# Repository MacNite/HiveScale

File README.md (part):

# HiveHub

> **Project renamed: HiveScale → HiveHub.** The project outgrew its original
> "dual scale" scope and now acts as a **data collector / hub for many different
> types of beehive sensors and scales** (up to 16 hives per ESP32), so the name
> was changed to match. A few internal identifiers — the database measurement
> columns, the OTA `target` value, the Docker image name (`…/hivescale-api`), the
> device's stored-config (NVS) namespace and MQTT topics — still use the old
> `hivescale` name on purpose: changing them would need data/firmware migrations
> and could strand existing measurements or deployed-device config. The
> third-party **beehivemonitoring.com "HiveScale"** wireless weight scale is an
> unrelated product and keeps its own name.

**Hardware status: all published PCBs are tested and working.** The recommended build is the **XIAO ESP32-C6 on the Scale Module V0.4** with **NAU7802**, **MAX17048**, **TPS63020**, **TP4056**, RTC, SD card and SHT40 — optionally expanded to **16 scales** with the NAU7802 breakout PCB (TCA9548A mux + up to 8× NAU7802). See [pcb-design/README.md](pcb-design/README.md). The old ESP32 30-pin board is obsolete and no longer recommended.

**HiveHub is an ESP32-based data collector for beehive sensors and scales.** It
gathers weight, temperature, humidity, sound, vibration, power state, and network
state from one or more hives (up to 16 per ESP32) and sends the readings to a
self-hosted FastAPI backend backed by PostgreSQL, where they can be displayed in
[HivePal](https://github.com/martinhrvn/hive-pal).

### Natively supported sensors

Every sensor is optional and compiled in per device — HiveHub reads the
following directly on the ESP32:

- **Ambient sensor (SHT4x / SHT3x / BME280)** — one device-level outside-hive
  sensor on the shared I2C bus, selectable at build time: SHT4x/SHT40 (default)
  or SHT3x for temperature + humidity, or a BME280 which additionally reports
  barometric pressure (`ambient_pressure_hpa`).
- **DS18B20** — per-hive in-hive temperature probes (1-Wire).
- **INMP441** — in-hive sound via I2S MEMS microphones with per-band FFT.
- **MAX17048** — LiPo battery voltage, state-of-charge, and low-battery alerts (I2C).
- **Wired load cells via HX711 or NAU7802** — the hive scales themselves; NAU7802
  over I2C (optionally behind a TCA9548A mux) scales to many channels for
  multi-hive setups.

On top of these wired sensors, HiveHub also bridges a range of wireless BLE/GATT
sensors and scales (HolyIot, RuuviTag, HiveInside, and beehivemonitoring.com
HiveHeart / HiveScale devices) — see [Features](#features) below.

> 🌐 **Website & setup guide:** a small static site lives in [`website/`](website/) — a
> feature overview, a step-by-step setup guide, a complete
> ["Build your own" guide](website/build.html) (BOM with price estimates, wiring,
> firmware, backend — downloadable as PDF), and an in-browser
> [`secrets.h` configurator](website/configurator.html) that builds your firmware
> config (sensors, BLE/GATT options, power modules) without hand-editing macros.
> It deploys to GitHub Pages via `.github/workflows/pages.yml`
> (enable **Settings → Pages → Source: GitHub Actions**), e.g.
> `https://macnite.github.io/HiveHub/`.

---

## Features

Every sensor is optional and compiled in per device — start with weight and add the rest.

- **Dual load cells** — two HX711 amplifiers drive two independent hive scales (the one always-on measurement).
- **Backend load-cell temperature compensation** — corrects HX711 thermal drift on read from the stored raw values; see [docs/temperature-compensation.md](docs/temperature-compensation.md).
- **Per-hive temperature** — optional DS18B20 probes on a shared 1-Wire bus (off by default), or an in-hive BLE sensor as the source.
- **Per-hive in-hive sound** — optional INMP441 stereo I2S microphones with per-band FFT (off by default).
- **Per-hive vibration** — from a paired in-hive BLE sensor (a HiveInside nRF54LM20A gives full FFT bands; a HolyIot/RuuviTag beacon gives a low-rate magnitude), capturing the ~20 Hz pre-swarm signal microphones miss. (The old wired LIS3DH/LIS2DH12 driver has been removed — in-hive vibration is BLE-only.)
- **In-hive BLE sensors** — pair up to two battery beacons (HolyIot 25015, RuuviTag, HiveInside nRF54LM20A, or beehivemonitoring.com HiveHeart) for temperature/humidity/pressure/vibration with no wiring. Note that a HiveHeart is read over GATT and accepts only **one** connection at a time, so HiveHub, the beehivemonitoring Hub and the beehivemonitoring app cannot share one — see [beehivemonitoring-gatt.md](docs/beehivemonitoring-gatt.md#one-reader-at-a-time).
- **Ambient temperature & humidity** — one selectable device-level I2C sensor: SHT4x/SHT40 (default), SHT3x, or a BME280 that also reports barometric pressure (`ambient_pressure_hpa`). Picked at build time (`ENABLE_SHT4X_AMBIENT` / `ENABLE_SHT3X_AMBIENT` / `ENABLE_BME280_AMBIENT`).
- **RTC timekeeping** — a DS3231 timestamps measurements without depending on NTP.
- **SD card cache & backup** — local buffering when uploads fail, plus an append-only persistent backup that can be downloaded in AP mode and re-imported via HivePal.
- **Claim-code pairing** — claim devices from HivePal without manual database setup.
- **Remote configuration & commands** — sampling interval, scale offsets/factors, calibration, OTA checks, provisioning, reboot, Wi-Fi reset, and factory reset.
- **OTA firmware updates** — owner-scoped releases with an accept-to-apply gate; the device also relays firmware over BLE GATT to a HiveInside sensor or a HiveTraffic counter. Both relays are version-gated and explicit: publishing a release never pushes it to a sub-device on its own.
- **Wi-Fi provisioning portal** — opened by the setup button (or remotely with a `start_provisioning` command) for field configuration, including pairing wireless sensors.
- **[Inspection mode](docs/inspection-mode.md)** — one press of the external button, a dashboard switch or a HivePal API call marks the window while a hive is open, so the 40 kg step from lifting two supers stays out of the charts, insights and alert rules. Nothing is deleted: the readings remain in the database and in every export.
- **Multi-network Wi-Fi** — up to three saved networks.
- **Hive audio (optional)** — ask a paired HiveInside node (firmware 0.6.2+) to record 10–60 seconds from inside the hive, then play it back in the dashboard. The hub collects the request on its next wake, so a recording arrives within one reporting interval rather than instantly. Authenticated with a shared key and stored as WAV on your own server. Useful for checking what an insight flagged — or just for listening to the bees. See [Listening to a hive](docs/audio-recording.md).
- **Insights** — backend auto-evaluation of weight, temperature, sound, vibration, and entrance traffic per hive, based on [these publications](docs/insights-sources-tldr.md).
- **Insight alert notifications (optional)** — get swarm / robbing / winter-risk alerts by **e-mail (SMTP)** and/or **Web Push** to your phone or an installable dashboard PWA (Android, iOS 16.4+, desktop) when an insight first fires or escalates. Off by default; see [Insight alert notifications](docs/notifications.md).
- **Optional off-grid mode** — solar/LiPo charging (CN3791 MPPT + TPS63020) with MAX17048 LiPo telemetry.
- **Optional entrance bee counters** — wireless [HiveTraffic](docs/hivetraffic-bee-counter.md) counters over **BLE/GATT only** (wired I2C BeeCounters are no longer supported).
- **Built-in web dashboard (optional)** — a dependency-free dashboard served from the backend at `/dashboard` for single-owner self-hosts, protected by **username + password login** (first visit runs a setup wizard; admin/viewer roles): cross-device hive comparison, charts for every data group, plus device-config editing, hive renaming, firmware/OTA and calibration controls, SD-backup import, and user management. Off by default (`ENABLE_LOCAL_DASHBOARD`); see [server/dashboard/README.md](server/dashboard/README.md) and the [live demo](https://macnite.github.io/HiveHub/dashboard-demo/).
- **Publish data for your website** — from **Device & admin → Publish data**, publish one chart (a metric, the hives you pick, a rolling period) and embed it in a club page, blog or shop with a one-line `<iframe>` — or fetch the same slice as JSON/CSV and draw it yourself. Everything else stays behind the login: a published link exposes only the labels you typed, no device IDs or other readings, and can be revoked at any time. See [Publish data](docs/publish-embed.md).
- **[HivePal](https://github.com/martinhrvn/hive-pal) integration** — dedicated `/api/v1/app/...` endpoints using a HivePal service key, per-user JWTs, and per-user access roles.
- **Optional MQTT bridge** — mirror every reading to an MQTT broker (Home Assistant, Node-RED, openHAB…) with Home Assistant auto-discovery, alongside the built-in PostgreSQL store. Off by default; see [MQTT / Home Assistant integration](#mqtt--home-assistant-integration).
- **PCB designs (tested and working)** — KiCad ESP32-C6 Scale Module (recommended) and NAU7802 breakout board with fabrication outputs, plus the Power Module and legacy 30-pin Scale Module.
- **Docker Compose deployment** — the API and PostgreSQL database.

---

## Repository structure

```text
HiveHub/
├── firmware/                   # ESP32 PlatformIO project (src/, include/)
├── server/                     # Python FastAPI backend, insights, migrations
│   ├── dashboard/              # Built-in login-protected web dashboard (served at /dashboard)
│   └── embed/                  # Public "Publish data" chart pages (served at /embed/chart/<token>)
├── docker/                     # Docker Compose deployment
├── website/                    # Static site + secrets.h configurator (GitHub Pages)
│   └── dashboard-demo/         # Backend-free dashboard demo (sample data)
├── docs/                       # Hardware, API, deployment, and feature docs
├── pcb-design/                 # KiCad breakout PCB design and fabrication files
├── test-data/                  # Mock server and decoder/insight unit tests
└── .github/workflows/          # CI: backend image build + website Pages deploy
```

---

## Hardware

### Core components

All links are affiliate links and support this project directly.

The recommended build is the **XIAO ESP32-C6 on the Scale Module V0.4** — the complete
bill of materials with price estimates and shop links lives on the
[**Build your own** page](website/build.html) (also downloadable as
[CSV](website/assets/hivehub-bom.csv)).

| Component | Role |
|---|---|
| Seeed Studio XIAO ESP32-C6 | Main controller (**recommended** — plugs into the Scale Module V0.4 PCB) |
| NAU7802 (I2C, on the Scale Module / breakout PCB) + [load cells](https://s.click.aliexpress.com/e/_c33VsCl7) | Weight measurement (**recommended** — 2 scales on the Scale Module, up to 16 via the NAU7802 breakout PCB with its TCA9548A mux + up to 8× NAU7802) |
| [SHT4x / SHT40](https://s.click.aliexpress.com/e/_c3CvaIKz) (or SHT3x / BME280) | Ambient temperature and humidity (BME280 also adds barometric pressure) |
| [DS3231 RTC](https://s.click.aliexpress.com/e/_c4mfPBtR) | Offline timekeeping (remove its 4.7 kΩ I2C pull-ups — see the I2C pull-up note in [docs/wiring.md](docs/wiring.md)) |
| [MicroSD card module](https://s.click.aliexpress.com/e/_c3oDcFM9) + card | Local cache and backup storage |
| [MAX17048](https://s.click.aliexpress.com/e/_c3JKEzrL) | LiPo battery gauge (on the Scale Module) |
| [TPS63020 buck-boost](https://s.click.aliexpress.com/e/_c2uscIy1) | Battery/5 V input to the regulated 3.3 V rail |
| [TP4056 USB-C charger](https://s.click.aliexpress.com/e/_c4beU1nL) | LiPo charging |
| [Momentary pushbutton](https://s.click.aliexpress.com/e/_c4sqg7Lx) | Provisioning and factory reset |
| [IP-rated enclosure](https://s.click.aliexpress.com/e/_c30msn9R), [glands](https://de.aliexpress.com/item/1005007921366362.html), frame hardware | Outdoor installation |
| [ESP32 Dev Board](https://s.click.aliexpress.com/e/_c3LV3nfF) + 2x [HX711](https://s.click.aliexpress.com/e/_c3DkGsAN) | Legacy 30-pin build (obsolete — no longer recommended) |

### Optional sensors (enable per device in `secrets.h`)

| Component | Firmware flag | Role |
|---|---|---|
| 2x [DS18B20 waterproof probes](https://s.click.aliexpress.com/e/_c4X4ktmv) | `ENABLE_DS18B20_HIVE_TEMP` | Internal hive temperature (or use an in-hive BLE sensor) |
| 2x [INMP441 sound sensors](https://s.click.aliexpress.com/e/_c313NoAd) | `ENABLE_INMP441_MICS` | Internal hive sound with per-band FFT |
| [MAX17048](https://s.click.aliexpress.com/e/_c3JKEzrL) | `ENABLE_MAX17048_BATTERY` | LiPo voltage, state-of-charge, and low-battery alert |
| In-hive BLE sensor (HolyIot 25015 / RuuviTag / HiveInside / HiveHeart) | `ENABLE_BLE_SCAN`, `ENABLE_BEEHIVE_GATT` | Temp / humidity / pressure / vibration, no wiring — paired by MAC |
| [CN3791 solar charger](https://s.click.aliexpress.com/e/_c4T7Ve5x) · [10 Ah LiPo](https://s.click.aliexpress.com/e/_c45jfAGv) · [6 V 4.5 W solar panel](https://s.click.aliexpress.com/e/_c3njKuVF) | Hardware only | Off-grid charging path feeding the Scale Module's TPS63020 |

### Optional bee counters

Entrance traffic counting (in/out bees) is **BLE/GATT-only**:

- **HiveTraffic** — the wireless [2026-easy-bee-counter](https://github.com/MacNite/2026-easy-bee-counter) board; see [docs/hivetraffic-bee-counter.md](docs/hivetraffic-bee-counter.md). Pairable to any hive.
- Wired I2C BeeCounters (the old `0x30`/`0x31` slave path, including firmware updates over I2C) are **no longer supported**. BeeCounter firmware is updated over BLE GATT instead — see [hivetraffic-bee-counter.md](docs/hivetraffic-bee-counter.md).

### Firmware pin mapping

Pins are defined in `firmware/include/config.h` (with optional per-device overrides in `secrets.h`). The firmware source is split into focused units under `firmware/src/` (`main.cpp`, `hivehub_network.cpp`, `portal.cpp`, `sensors.cpp`, `scale_bus.cpp`, `i2c_bus.cpp`, `hive_config.cpp`, `mics.cpp`, `ble_sensor.cpp`, `beehive_gatt.cpp`, `bee_counter_client.cpp`, `storage_power.cpp`, `device_prefs.cpp`, `status_led.cpp`, `globals.cpp`).

The table below is the **legacy 30-pin ESP32** map. The recommended **XIAO ESP32-C6** build (`pio run -e xiao_esp32c6`) has its own pin map — NAU7802 scales over I2C on D4/D5, DS18B20 on D1, SD on D3/D8–D10, button on D2, no HX711/INMP441 — see [docs/wiring.md](docs/wiring.md) and [pcb-design/README.md](pcb-design/README.md).

| Signal | GPIO | Notes |
|---|---:|---|
| HX711 #1 DOUT / SCK | 16 / 17 | Scale 1; SCK held high during deep sleep to power down the HX711 |
| HX711 #2 DOUT / SCK | 32 / 33 | Scale 2; SCK held high during deep sleep to power down the HX711 |
| DS18B20 1-Wire data | 4 | Shared bus for both probes; 4.7 kΩ pull-up to 3.3 V (`ENABLE_DS18B20_HIVE_TEMP`) |
| I2C SDA / SCL | 21 / 22 | RTC, SHT4x, NAU7802/TCA9548A, optional MAX17048 — shared bus at an explicit **100 kHz** |
| SD CS / SCK / MISO / MOSI | 5 / 18 / 23 / 19 | MicroSD over SPI |
| Setup button | 27 | `INPUT_PULLUP`; short press opens provisioning AP, long press factory resets |

> On the **XIAO ESP32-C6** (firmware 0.25.0+) the setup button is the board's on-board USER/BOOT button, and the external D2 button is the [inspection button](docs/inspection-mode.md). The 30-pin board above is unchanged. Note that GPIO9 cannot wake the C6 from deep sleep and holding it at power-up enters the serial bootloader, so on that board press and hold the USER button and the AP opens a second into the next wake (up to one send interval away) — or press RESET, release it, *then* hold BOOT to get there in under a minute (never hold BOOT across the RESET: that is the flashing gesture). For a sealed hub use **Start AP mode** in the dashboard — see [docs/ap-mode-sd-download.md](docs/ap-mode-sd-download.md).
| INMP441 BCLK / WS / SD | 14 / 13 / 34 | I2S, shared by both mics; GPIO34 is input-only (`ENABLE_INMP441_MICS`) |

> See [docs/wiring.md](docs/wiring.md) for detailed wiring and [pcb-design/README.md](pcb-design/README.md) for the KiCad breakout PCB pinout.

---

## Firmware setup

### Prerequisites

- PlatformIO (VS Code extension or CLI).

### Configuration

```bash
cp firmware/include/secrets.example.h firmware/include/secrets.h
```

Edit `firmware/include/secrets.h`:

```cpp
#define DEVICE_ID           "hive-001"
#define API_KEY             "your-api-key-here"   // unique per device — see note below
#define CLAIM_CODE          "ABCD-1234"
#define CLAIM_CODE_REVISION 1
#define API_BASE_URL        "https://your-backend-domain.com"   // HTTPS (TLS is verified)

#define WIFI1_SSID          "your-wifi-ssid-1"
#define WIFI1_PASS          "your-wifi-password-1"
// WIFI2_* and WIFI3_* are optional fallbacks
```

Values in `secrets.h` seed the device's persistent `Preferences` on first boot. Later changes are usually made through the backend or provisioning portal. Set `FORCE_RESEED true` only when you intentionally want to overwrite stored preferences from the build file.

> **Per-device API key:** give each device its own unique `API_KEY` (generate one
> with `openssl rand -hex 32`). The backend registers the key against the device's
> `device_id` on first contact and rejects mismatches afterwards, so a leaked key
> only affects that one device. It no longer has to match the server's `API_KEY`
> environment variable — that value is now only the master/admin key for tooling.

### TLS / certificate verification

The firmware verifies the backend's TLS certificate. It ships the ISRG Root X1
(Let's Encrypt) root CA in `firmware/include/ca_cert.h` and syncs the clock over
NTP after connecting so validity can be checked. Therefore:

- By default, the backend must be reachable over **HTTPS with a valid certificate** (a reverse proxy with Let's Encrypt is the simplest setup).
- For a CA other than Let's Encrypt, replace the certificate in `firmware/include/ca_cert.h` (instructions are in that file).
- NTP (UDP port 123) must be reachable from the device's network.

For a trusted LAN deployment that cannot use TLS, add the following **firmware
build setting** to `secrets.h` and use an `http://` `API_BASE_URL` (for example,
`http://192.168.1.10:31115`). This is intentionally not a server environment
variable: the ESP32 selects its transport before it can contact the server.

```cpp
#define ALLOW_INSECURE_HTTP 1
```

The opt-in keeps HTTPS working and certificate-verified, but also permits HTTP
for API requests and OTA downloads. HTTP exposes the per-device API key,
measurements, commands, and firmware image to anyone able to observe or alter
traffic, so use it only on an isolated, trusted network.

### Optional modules

Optional sensors are enabled per build in `secrets.h`. The defaults shipped in `secrets.example.h`:

```cpp
#define ENABLE_DS18B20_HIVE_TEMP 0   // wired in-hive temperature probes (default off)
#define ENABLE_INMP441_MICS      0   // stereo I2S mics + per-band FFT (default off)
#define ENABLE_BLE_SCAN          1   // in-hive BLE sensor bridge — HolyIot/RuuviTag/HiveInside (default on)
#define ENABLE_BEEHIVE_GATT      0   // beehivemonitoring.com HiveHeart / HiveScale over GATT (default off)
#define ENABLE_MAX17048_BATTERY  0   // LiPo fuel-gauge telemetry (default off)
```

The [secrets.h configurator](website/configurator.html) writes these (and the wireless-sensor macros) for you.

> Cellular (SIM7080G) transport is no longer part of this firmware. LTE, solar,
> and battery handling now live on a separate **Power Module** that connects to
> the Scale Module over I2C/ESP-NOW. The ESP32 firmware itself is Wi-Fi only.

### Download a prebuilt image (no toolchain)

Every CI run builds both targets and attaches the images to the run, and every
tagged release carries them permanently:

| Where | What you get | Keeps |
|---|---|---|
| [Releases](../../releases) | Images for the tagged version | forever |
| [Actions → CI](../../actions/workflows/ci.yml) → a run → *Artifacts* | Images for that exact commit, incl. branches and PRs | 90 days |

Two files per board — `esp32-c6` (XIAO, recommended) and `esp32` (legacy 30-pin):

- **`hivehub_<board>_<version>_full.bin`** — bootloader + partition table +
  otadata + application, written as a single file at offset `0x0`. Use this for
  a blank board.
- **`hivehub_<board>_<version>.bin`** — application image only. This is the file
  to upload to your backend for OTA, or to the dashboard's firmware uploader.

```bash
# XIAO ESP32-C6, blank board
esptool.py --chip esp32c6 --port /dev/ttyACM0 write_flash 0x0 hivehub_esp32-c6_0.24.7_full.bin

# Legacy 30-pin ESP32
esptool.py --chip esp32 --port /dev/ttyUSB0 write_flash 0x0 hivehub_esp32_0.24.7_full.bin
```

Prebuilt images contain no `secrets.h`: Wi-Fi, server URL and API key are set on
the device through the [setup portal](#wi-fi-provisioning-portal), and the
compile-time feature flags stay at their defaults. To change a flag (DS18B20,
INMP441 mics, GATT sensors …) you still need a local build.

`firmware/ci/package_build.sh <env>` produces the same files locally after a
`pio run`.

### Flash from source

```bash
cd firmware
pio run --target upload
pio device monitor   # 115200 baud
```

### PlatformIO dependencies

`platformio.ini` installs the required libraries automatically:

- `bogde/HX711`, `paulstoffregen/OneWire`, `milesburton/DallasTemperature`
- `adafruit/Adafruit SHT4x Library`, `adafruit/RTClib`, `bblanchon/ArduinoJson`
- `kosme/arduinoFFT` — per-band FFT for the INMP441 mics and the vibration bands
- `h2zero/NimBLE-Arduino` (2.x) — the in-hive BLE sensor bridge and GATT clients

Optional libraries:

- `sparkfun/SparkFun MAX1704x Fuel Gauge Arduino Library` — `ENABLE_MAX17048_BATTERY`

---

## Wi-Fi provisioning portal

Press the setup button (the on-board USER button on the XIAO ESP32-C6, GPIO27 on the legacy 30-pin board) to manage field configuration without reflashing. A hub already sealed in an enclosure can open the same portal remotely with a `start_provisioning` command from the dashboard or API.

| Action | Result |
|---|---|
| Short press | Starts `HiveHub-Setup-XXXX` AP; open `http://192.168.4.1` |
| Long press, 10 seconds | Clears stored Preferences and reboots |

The portal is organised **by hive**: it edits Wi-Fi networks, backend URL, device ID, claim code and API settings, and manages the hive registry — add a hive, pick its scale source (auto-detected NAU7802 channels or a wireless HiveScale) and one in-hive sensor (a DS18B20 probe by ROM or a BLE/GATT sensor by MAC, with a built-in **BLE scan**). It also offers live **scale calibration** (tare + known weight, fully offline) and an **SD-card download** (TAR) of the on-device backup. It closes automatically after 10 minutes. See [docs/multi-hive.md](docs/multi-hive.md) and [docs/ap-mode-sd-download.md](docs/ap-mode-sd-download.md).

---

## Server setup

### Docker Compose

```bash
cd docker
cp .env.example .env
# edit API_KEY, HIVEPAL_SERVICE_API_KEY, HIVEPAL_JWT_SECRET, POSTGRES_PASSWORD,
# PUBLIC_BASE_URL, and the database volume path in docker-compose.yml
docker compose up -d
```

The API listens on port `31115` by default. `API_KEY` and `POSTGRES_PASSWORD`
are **required** — compose refuses to start without them rather than falling
back to insecure defaults. Uploaded OTA firmware binaries persist in the
`firmware-data` volume.

| Setting | Default |
|---|---|
| API image | `ghcr.io/macnite/hivehub:latest` |
| API port | `31115` |
| Database image | `postgres:16-alpine` |
| Database name/user | `hivescale` |

See [docs/docker-install.md](docs/docker-install.md) and [docs/truenas-install.md](docs/truenas-install.md) for full guides.

### Manual / local

```bash
cd server
pip install -r requirements.txt
DATABASE_URL="postgresql://hivescale:password@localhost:5432/hivescale" \
API_KEY="your-master-admin-key" \
HIVEPAL_SERVICE_API_KEY="your-hivepal-service-key" \
HIVEPAL_JWT_SECRET="must-match-hivepal-jwt-secret" \
PUBLIC_BASE_URL="https://your-domain.example.com" \
uvicorn main:app --host 0.0.0.0 --port 8000
```

### Environment variables

| Variable | Required | Description |
|---|---|---|
| `DATABASE_URL` | Yes | PostgreSQL connection string |
| `API_KEY` | Yes | Master/admin key in `X-API-Key` for server-to-server tooling (firmware-release registration, command queueing, latest-measurements, time). Devices use their own per-device keys, registered on first contact. |
| `HIVEPAL_SERVICE_API_KEY` | Yes, for HivePal | Service key sent by HivePal in `X-HivePal-Service-Key` |
| `HIVEPAL_JWT_SECRET` | Yes, for HivePal | Shared HS256 secret used to verify the per-user `Authorization: Bearer` tokens HivePal sends. Must match HivePal's `JWT_SECRET`. |
| `PUBLIC_BASE_URL` | Recommended | Public base URL used for OTA firmware download links |
| `FIRMWARE_DIR` | Optional | Firmware binary directory, default `/app/firmware` |
| `DB_POOL_MIN_SIZE` / `DB_POOL_MAX_SIZE` | Optional | DB connection pool bounds (default `1` / `10`) |
| `RATE_LIMIT_ENABLED` / `RATE_LIMIT_DEFAULT` | Optional | Per-client-IP rate limit (default on, `120/minute`) |
| `MAX_BODY_BYTES` / `MAX_FIRMWARE_BYTES` | Optional | Request-body and firmware-upload size caps (default 256 KiB / 16 MiB) |
| `ENABLE_LOCAL_DASHBOARD` | Optional | Serve the built-in **login-protected** dashboard at `/dashboard` and its `/api/v1/local/*` API (default off). It serves every device on the server behind one login, so keep it off on multi-tenant deployments. |
| `DASHBOARD_SESSION_SECRET` / `DASHBOARD_SESSION_TTL_HOURS` / `DASHBOARD_COOKIE_SECURE` | Optional | Dashboard login-session settings: signing secret (auto-generated and persisted when blank), session lifetime (default `168` h), HTTPS-only cookie flag |
| `ENABLE_PUBLIC_EMBEDS` | Optional | Allow the dashboard's **Device & admin → Publish data** panel to serve individual published charts without a login, for embedding in a website (default on; nothing is public until an admin publishes it, and the panel is hidden when this is off). See [Publish data](docs/publish-embed.md). |
| `TRUST_PROXY_HEADERS` | Optional | Trust `CF-Connecting-IP` / `X-Forwarded-For` for rate-limit client IPs (default `false`; set `true` only behind a reverse proxy that overwrites these headers, otherwise a direct client can spoof them to dodge the limiter) |
| `INSIGHTS_RECONCILE_*` | Optional | Background insight-history reconciliation (see `server/.env.example`) |
| `SMTP_*` / `NOTIFY_MIN_SEVERITY` | Optional | E-mail channel for insight alert notifications (off by default — see [Insight alert notifications](docs/notifications.md)) |
| `WEB_PUSH_ENABLED` / `VAPID_*` | Optional | Web Push channel for insight alert notifications (off by default — see [Insight alert notifications](docs/notifications.md)) |
| `MQTT_*` | Optional | MQTT bridge to Home Assistant / Node-RED / openHAB (off by default — see [MQTT / Home Assistant integration](#mqtt--home-assistant-integration)) |
| `TZ` | Optional | Server timezone, for example `Europe/Berlin` |

The backend auto-creates tables and runs idempotent `ALTER TABLE` statements on startup; the SQL files in `server/migrations/` can also be applied manually.

---

## MQTT / Home Assistant integration

The backend can **optionally** mirror every measurement to an MQTT broker in
addition to storing it in PostgreSQL — so HiveHub data flows into
[Home Assistant](https://www.home-assistant.io/), Node-RED, openHAB or any MQTT
consumer. It is **off by default** and purely additive: the bridge runs in a
background thread and is fail-soft, so a broker outage never affects ingestion
or the API.

Enable it by setting `MQTT_ENABLED=true` and pointing `MQTT_HOST` at your broker
(see `server/.env.example` / `docker/.env.example` for the full list):

```bash
MQTT_ENABLED=true
MQTT_HOST=192.168.1.10        # your broker (e.g. the Mosquitto add-on)
MQTT_PORT=1883
MQTT_USERNAME=hivescale       # optional
MQTT_PASSWORD=...             # optional
MQTT_HA_DISCOVERY=true        # auto-create Home Assistant entities
```

### Topics

With `MQTT_BASE_TOPIC=hivescale` (the default):

| Topic | Payload |
|---|---|
| `hivescale/bridge/availability` | `online` / `offline` (bridge last-will) |
| `hivescale/<device_id>/availability` | `online` / `offline` (per device) |
| `hivescale/<device_id>/state` | Retained JSON of the latest reading (every non-null measurement field) |

### Home Assistant

When `MQTT_HA_DISCOVERY=true`, the bridge publishes
[MQTT-discovery](https://www.home-assistant.io/integrations/mqtt/#mqtt-discovery)
configs the first time it sees each device. Home Assistant then automatically
creates one device per scale with a curated set of sensors — scale weights,
hive/ambient temperature & humidity, battery voltage/charge, solar power, Wi-Fi
signal, and bee-counter totals. Any in-hive wireless modules (a
beehivemonitoring.com HiveHeart/HiveScale or a HolyIOT BLE sensor) are exposed
as their own Home Assistant devices, nested under the hub, each carrying its own
full telemetry — temperature, humidity, battery and link signal (plus weight and
pressure for the scale, and sound frequency/energy/peak for the HiveHeart). Those
per-device temperature/humidity entities are published even though the hive's
resolved temperature/humidity also appear on the hub device, so a hive fitted
with several modules surfaces each one's readings separately. All other fields
remain available in the raw `state` JSON for custom templated sensors. Just make sure the
[MQTT integration](https://www.home-assistant.io/integrations/mqtt/) is set up
and pointed at the same broker.

See [docs/mqtt.md](docs/mqtt.md) for the full topic layout, every configuration
variable, and the per-hive / per-module Home Assistant discovery details.

---

## API overview

Interactive Swagger docs are at `http://<host>:31115/docs`. See [docs/api.md](docs/api.md) for the full reference and schemas.

### Device-facing endpoints

Require the `X-API-Key` header (per-device key, except where noted as master/admin).

| Method | Endpoint | Description |
|---|---|---|
| `GET` | `/health` | Health check (no auth) |
| `GET` | `/api/v1/time` | UTC server time for RTC sync (master/admin) |
| `POST` | `/api/v1/measurements` | Submit a measurement (incl. optional telemetry) |
| `GET` | `/api/v1/measurements/latest` | Latest measurements for dashboards (master/admin) |
| `GET`/`PATCH` | `/api/v1/devices/{id}/config` | Get / update device configuration |
| `GET` | `/api/v1/devices/{id}/firmware` | Check for a firmware update (`?version=`, `?target=hivescale`, `?board=`) |
| `POST` | `/api/v1/firmware/releases` | Register a firmware release (master/admin) |
| `GET` | `/firmware/{filename}` | Download a firmware binary |
| `POST` | `/api/v1/devices/{id}/commands` | Queue a remote command (master/admin) |
| `POST` | `/api/v1/devices/{id}/commands/update-hiveinside` | Queue a HiveInside OTA relay over BLE (`?slot=` hive index, `?force=`) |
| `GET` | `/api/v1/devices/{id}/commands/next` | Claim next pending command |
| `POST` | `/api/v1/devices/{id}/commands/{cmd_id}/result` | Report command result |

### App endpoints for HivePal

Require both `X-HivePal-Service-Key` and a per-user `Authorization: Bearer <hivepal-jwt>` token (verified with `HIVEPAL_JWT_SECRET`).

| Method | Endpoint | Description |
|---|---|---|
| `POST` | `/api/v1/app/devices/claim` | Claim a device by claim code |
| `GET`/`DELETE` | `/api/v1/app/devices` · `/{id}` | List devices · remove own membership (releases the device when it was the last one) |
| `DELETE` | `/api/v1/app/devices/{id}/claim` | Release the device outright: drop every member and unclaim it (owner) |
| `GET`/`PATCH` | `/api/v1/app/devices/{id}/config` | Get / update config (incl. `tempco_*`) |
| `GET`/`PATCH` | `/api/v1/app/devices/{id}/channels` | List / update scale display names |
| `GET` | `/api/v1/app/devices/{id}/measurements[/latest]` | Measurements (with date filter) / latest |
| `POST` | `/api/v1/app/devices/{id}/measurements/import` | Bulk-import SD-card backup rows (idempotent) |
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
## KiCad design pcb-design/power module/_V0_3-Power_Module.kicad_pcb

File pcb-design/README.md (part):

# current state of PCB-Design (as of 4th July 2026)

Scale Module: V0.2 is  tested and works (expansion header and beecounter header are untested): on the 2nd sound input terminal the silk screen print is wrong. pinout on this connector is: 3.3v / 3.3v / GND / BCLK / WS / SD
Scale Module: completely untested but only minor layout-changes and silk screen optimisation
Power Module: V0.3 is only tested for use with the buck-boost converter. Solar charging, Lipo Connection, USB charging are currently untested.

# HiveScale PCB Design — Scale Module V0.2

This directory contains the KiCad schematic and PCB layout for the HiveScale **Scale Module**. It is a breakout board that accepts off-the-shelf modules on pin headers — no SMD soldering required. All modules are simply plugged in.

The Scale Module is the central board of the HiveScale system. Power and connectivity (LTE, solar, battery) are handled by a separate **Power Module**, which connects to this board via I2C or ESPnow.

---

## Modules on board

| Ref | Module | Interface | Notes |
|---|---|---|---|
| J1, J2 | ESP32 30-pin Dev Board | — | Main controller; plugs into left and right header rows |
| J4, J7 | HX711 Scale 1 | Digital I/O | Load cell amplifier for scale platform 1 |
| J3, J8 | HX711 Scale 2 | Digital I/O | Load cell amplifier for scale platform 2 |
| J11 | Load cell 1 input | Screw terminal | Direct load cell wires for scale 1 |
| J12 | Load cell 2 input | Screw terminal | Direct load cell wires for scale 2 |
| J9 | SD module | SPI | MicroSD card for local cache and backup |
| J5 | DS3231 RTC | I2C | Real-time clock with coin cell backup |
| J13 | DS18B20 Hive 1 | 1-Wire | Internal hive temperature probe |
| J14 | DS18B20 Hive 2 | 1-Wire | Internal hive temperature probe |
| J15 | SHT40 Ambient | I2C | External ambient temperature and humidity |
| J6 | INMP441 Sound Sensor Hive 1 | I2S | MEMS microphone — left channel |
| J16 | INMP441 Sound Sensor Hive 2 | I2S | MEMS microphone — right channel |
| J20 | BeeCounter | Digital I/O | Bee traffic counter module |
| SW1 | Pushbutton | Digital input | Short press: provisioning AP; long press: factory reset |
| J10 | Power In | — | 5 V supply input |
| J19 | Power Module Header | — | Connection to separate Power Module |
| J17 | I2C expansion | I2C | Shared bus header for additional I2C devices |
| J18 | Expansion Header (12-pin) | Mixed | GPIO breakout for future use |

---

## ESP32 pin mapping

| Signal | ESP32 GPIO | Direction | Notes |
|---|---:|---|---|
| HX711 #1 DOUT | 16 | Input | Scale 1 data |
| HX711 #1 SCK | 17 | Output | Scale 1 clock; held HIGH during deep sleep to power down HX711 |
| HX711 #2 DOUT | 32 | Input | Scale 2 data |
| HX711 #2 SCK | 33 | Output | Scale 2 clock; held HIGH during deep sleep to power down HX711 |
| DS18B20 1-Wire | 4 | Bidirectional | Shared bus for both hive probes; 4.7 kΩ pull-up to 3.3 V on board |
| I2C SDA | 21 | Bidirectional | RTC, SHT40, I2C expansion |
| I2C SCL | 22 | Output | RTC, SHT40, I2C expansion; 4.7 kΩ pull-up to 3.3 V on board |
| SD CS | 5 | Output | SD card chip select |
| SD SCK | 18 | Output | SPI clock |
| SD MISO | 23 | Input | |
| SD MOSI | 19 | Output | |
| Setup button | 27 | Input | `INPUT_PULLUP`, active low |
| INMP441 BCLK | 14 | Output | I2S bit clock shared by both microphones |
| INMP441 WS (LRCLK) | 13 | Output | I2S word select shared by both microphones |
| INMP441 SD (data) | 34 | Input | I2S data; GPIO34 is input-only on ESP32 |
| BeeCounter signal A | 12 | Input | Beam sensor channel A |
| BeeCounter signal B | 15 | Input | Beam sensor channel B (see schematic) |

> GPIO34 is input-only and has no internal pull-up. The INMP441 SD line is an open-drain output; pull-up on board is not required but confirm with your module's datasheet.

---

## INMP441 stereo microphone wiring

Both INMP441 modules share a single I2S bus. Channel selection is hardware-configured via the **L/R pin** on each module:

| Module | Connector | L/R pin | Channel |
|---|---|---|---|
| Sound Sensor Hive 1 | J6 | GND | Left channel |
| Sound Sensor Hive 2 | J16 | 3.3 V | Right channel |

The L/R assignment is **not visible in the schematic** — it is determined by which power rail is connected to the L/R pad on each module. The PCB header for J6 ties L/R to GND and the header for J16 ties L/R to 3.3 V. Verify this during layout and assembly.

All three bus lines (BCLK, WS, SD) are shared between both modules. Each module must have VDD connected to 3.3 V and GND to GND.

```
INMP441 Hive 1 (J6):  VDD -> 3.3V  GND -> GND  BCLK -> GPIO14  WS -> GPIO13  SD -> GPIO34  L/R -> GND
INMP441 Hive 2 (J16): VDD -> 3.3V  GND -> GND  BCLK -> GPIO14  WS -> GPIO13  SD -> GPIO34  L/R -> 3.3V
```

---

## BeeCounter wiring (J20)

The BeeCounter module connects via three pins:

| J20 pin | Signal |
|---|---|
| 1 | GPIO13 |
| 2 | GPIO14 |
| 3 | GND |

> Note: GPIO13 is shared with INMP441 WS. In firmware, the I2S peripheral takes ownership of GPIO13 during audio sampling. Confirm that the BeeCounter firmware logic does not conflict with the I2S peripheral when both are active. If conflicts arise during development, move BeeCounter to one of the GPIO pins exposed on the expansion header (J18).

> **Firmware integration note:** the current HiveScale firmware
> (`firmware/src/bee_counter_client.cpp`) communicates with the BeeCounter as an
> **I2C slave** at addresses `0x30` (hive 1) / `0x31` (hive 2) on the shared bus
> (SDA GPIO21 / SCL GPIO22) — including the OTA-over-I2C firmware relay. Reconcile
> the J20 wiring above with the I2C bus before fabricating, and route the
> BeeCounter to SDA/SCL rather than the discrete GPIOs.

---

## I2C bus

| Device | Address |
|---|---|
| DS3231 RTC | `0x68` |
| SHT40 | `0x44` |

Both 4.7 kΩ pull-up resistors (SDA-4.7k1, SCL-4.7k1) are on board. Do not add additional pull-ups on plugged-in modules unless the total effective pull-up resistance becomes too low. If multiple I2C modules with built-in pull-ups are installed, verify the combined resistance.

---

## Power

The board is powered via J10 (Power In, 5 V) or through J19 (Power Module Header). The ESP32 and all 3.3 V peripherals are supplied from the ESP32 on-board regulator or from the Power Module.

- All module GNDs must share a common ground.
- Keep load-cell analog wiring away from any switching regulators or high-frequency signals.
- The SD card module and RTC backup coin cell are independently powered from 3.3 V.

---

## Connectors

### J1 — ESP32 left (TX/RX side), 15-pin

Carries UART, I2C, SD SPI, DS18B20, button, and several GPIO signals.

### J2 — ESP32 right (power/ADC side), 15-pin

Carries power rails, HX711 signals, INMP441 I2S signals, and ADC-capable GPIOs.

### J17 — I2C expansion, 6-pin

Exposes 3.3 V, GND, SDA, SCL for additional I2C devices.

### J18 — Expansion header, 12-pin

Breaks out remaining GPIOs for future expansion or custom peripherals.

### J19 — Power Module header

Connects to the separate Power Module (solar, battery, LTE) via I2C or ESPnow. Exact pinout depends on Power Module revision.

---

## Fabrication

Fabrication outputs are in the `fabrication/` subdirectory. Before ordering:

- Confirm all module header footprints match the physical modules you are using (pin pitch, row spacing).
- Verify the INMP441 L/R pin routing as described above.
- Verify pull-up resistor values on the I2C bus.
- Order a small prototype run before field deployment.

---

## Assembly notes

- Plug modules into headers — do not solder modules directly to the board.
- Install the DS3231 coin cell before sealing the enclosure.
- Route load-cell wiring away from the SD module and any switching supplies.
- Label Scale 1 and Scale 2 wiring at both the load-cell combinator and the PCB terminals.
- Use ferrules or locking connectors on load-cell screw terminals where vibration is expected.
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
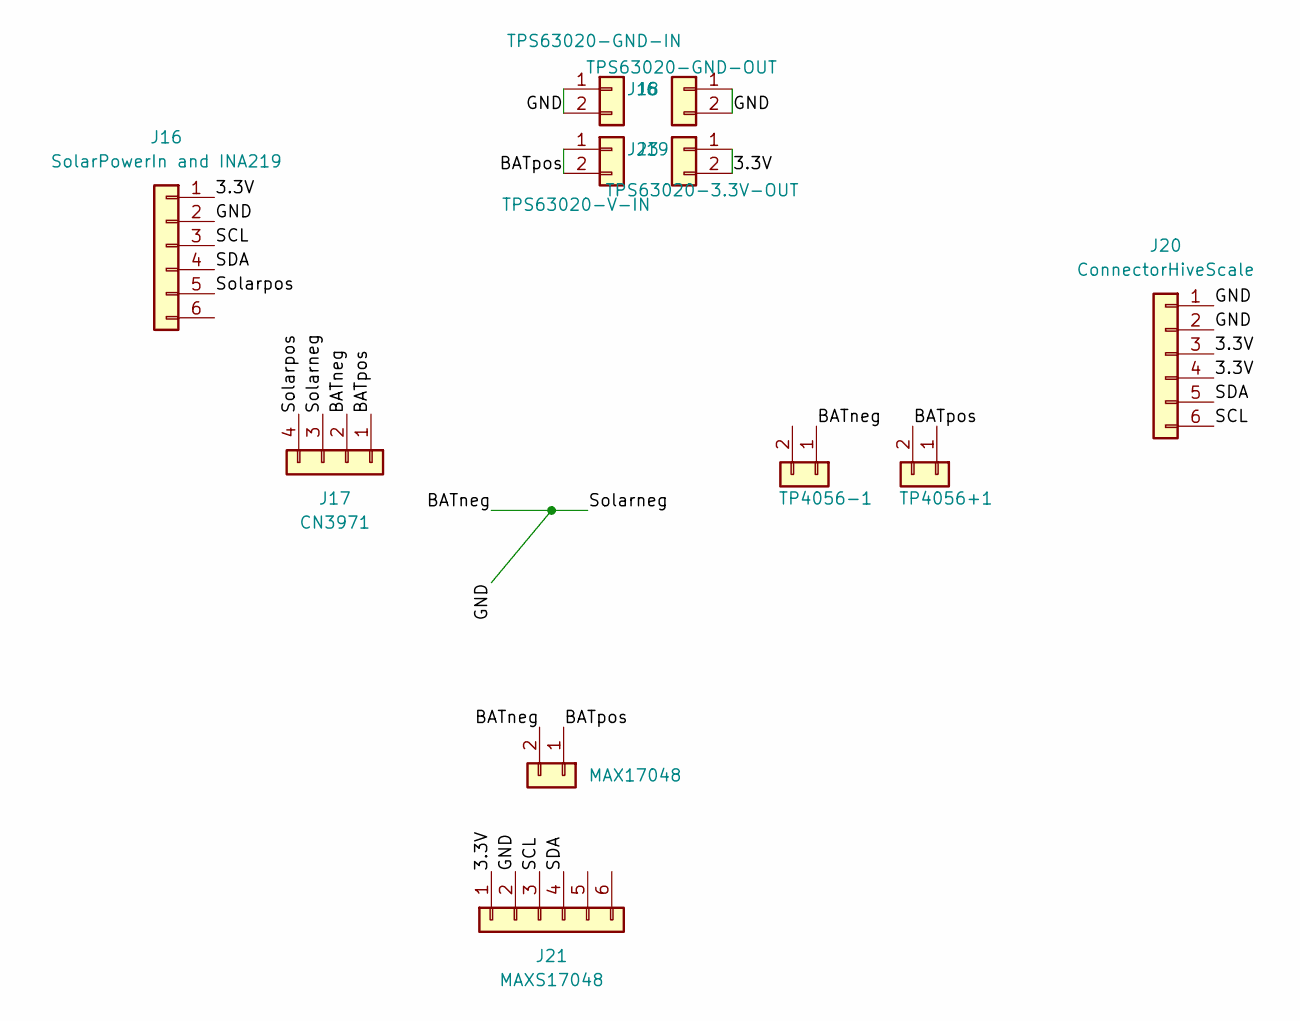
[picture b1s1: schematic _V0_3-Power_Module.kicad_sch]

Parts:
J6: TPS63020-GND-IN; PinSocket_1x02_P2.54mm_Vertical
J16: SolarPowerIn and INA219; PinSocket_1x06_P2.54mm_Vertical
J17: CN3971; PinSocket_1x04_P2.54mm_Vertical
J18: TPS63020-GND-OUT; PinSocket_1x02_P2.54mm_Vertical
J19: TPS63020-V-IN; PinSocket_1x02_P2.54mm_Vertical
J20: ConnectorHiveScale; PinHeader_1x06_P2.54mm_Vertical
J21: MAXS17048; PinSocket_1x06_P2.54mm_Vertical
J23: TPS63020-3.3V-OUT; PinSocket_1x02_P2.54mm_Vertical
MAX17048: BatteryMAX17048; PinSocket_1x02_P2.54mm_Vertical
TP4056+1, TP4056-1: BatteryMAX17048; PinSocket_1x02_P2.54mm_Vertical

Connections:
/3.3V: J16.1, J20.3, J20.4, J21.1, J23.1, J23.2
/BATneg: J6.1, J6.2, J16.2, J17.2, J17.3, J18.1, J18.2, J20.1, J20.2, J21.2, MAX17048.2, TP4056-1.1 (Pin_1_1)
/BATpos: J17.1, J19.1, J19.2, MAX17048.1, TP4056+1.2 (Pin_2_2)
/SCL: J16.3, J20.6, J21.3
/SDA: J16.4, J20.5, J21.4
/Solarpos: J16.5, J17.4

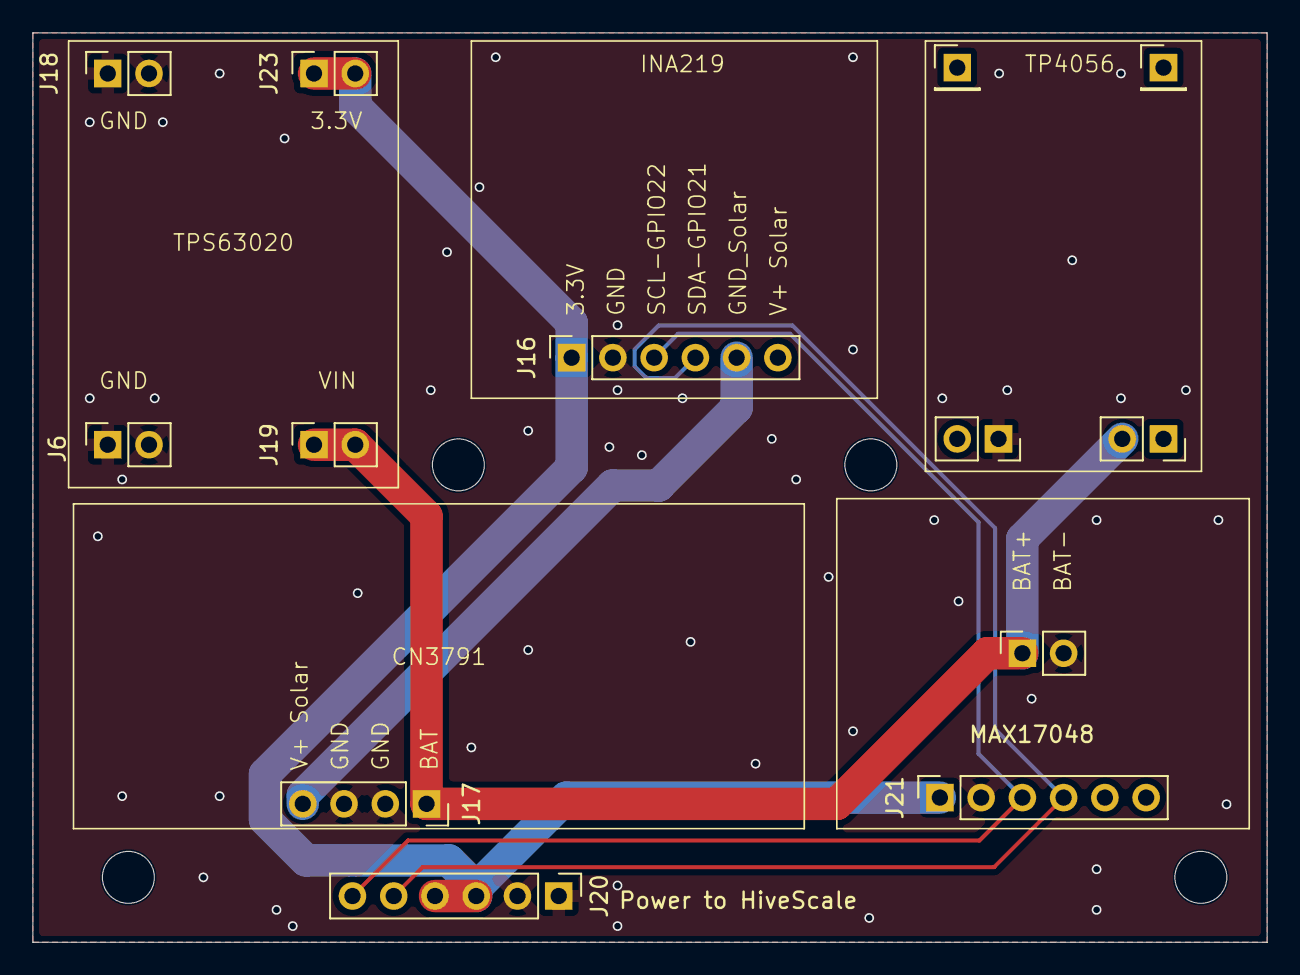
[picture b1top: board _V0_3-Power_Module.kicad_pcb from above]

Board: 2 copper layers, 76.0 x 56.0 mm, 17 parts (0 on the bottom side), 6 nets.

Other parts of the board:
m3-bl, m3-br, m3-tl, m3-tr: MountingHole_3.2mm_M3
stabilizer_usb_1, stabilizer_usb_2: PinHeader_1x01_P2.54mm_Vertical

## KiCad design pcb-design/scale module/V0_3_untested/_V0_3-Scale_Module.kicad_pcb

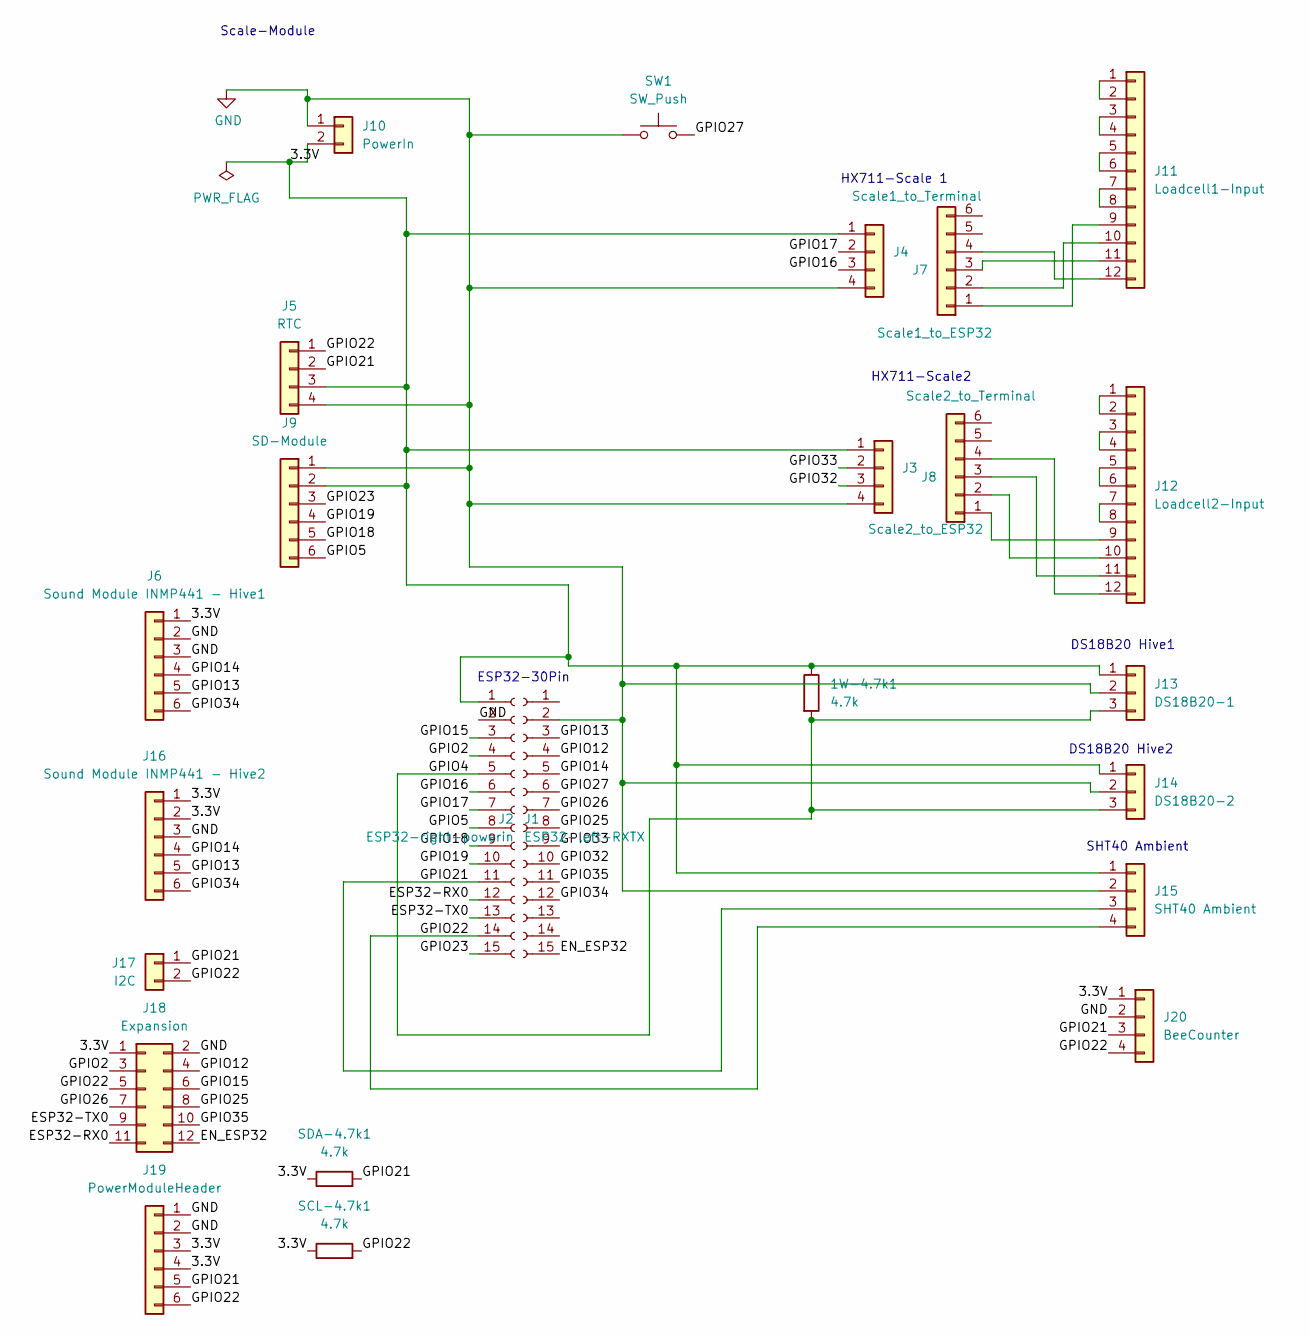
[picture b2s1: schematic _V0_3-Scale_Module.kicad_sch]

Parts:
1W-4.7k1: 4.7k; R_Axial_DIN0207_L6.3mm_D2.5mm_P7.62mm_Horizontal
J1: ESP32-left-RXTX; PinSocket_1x15_P2.54mm_Vertical
J2: ESP32-right-powerin; PinHeader_1x15_P2.54mm_Vertical
J3: Scale2_to_ESP32; PinSocket_1x04_P2.54mm_Vertical
J4: Scale1_to_ESP32; PinSocket_1x04_P2.54mm_Vertical
J5: RTC; PinSocket_1x04_P2.54mm_Vertical
J6: Sound Module INMP441 - Hive1; TerminalBlock_Xinya_XY308-2.54-6P_1x06_P2.54mm_Horizontal
J7: Scale1_to_Terminal; PinSocket_1x06_P2.54mm_Vertical
J8: Scale2_to_Terminal; PinSocket_1x06_P2.54mm_Vertical
J9: SD-Module; PinSocket_1x06_P2.54mm_Vertical
J10: PowerIn; TerminalBlock_Xinya_XY308-2.54-2P_1x02_P2.54mm_Horizontal
J11: Loadcell1-Input; TerminalBlock_Xinya_XY308-2.54-12P_1x12_P2.54mm_Horizontal
J12: Loadcell2-Input; TerminalBlock_Xinya_XY308-2.54-12P_1x12_P2.54mm_Horizontal
J13: DS18B20-1; TerminalBlock_Xinya_XY308-2.54-3P_1x03_P2.54mm_Horizontal
J14: DS18B20-2; TerminalBlock_Xinya_XY308-2.54-3P_1x03_P2.54mm_Horizontal
J15: SHT40 Ambient; TerminalBlock_Xinya_XY308-2.54-4P_1x04_P2.54mm_Horizontal
J16: Sound Module INMP441 - Hive2; TerminalBlock_Xinya_XY308-2.54-6P_1x06_P2.54mm_Horizontal
J17: I2C; TerminalBlock_Xinya_XY308-2.54-2P_1x02_P2.54mm_Horizontal
J18: Expansion; PinHeader_2x06_P2.54mm_Vertical
J19: PowerModuleHeader; PinHeader_1x06_P2.54mm_Vertical
J20: BeeCounter; TerminalBlock_Xinya_XY308-2.54-4P_1x04_P2.54mm_Horizontal
SCL-4.7k1: 4.7k; R_Axial_DIN0207_L6.3mm_D2.5mm_P7.62mm_Horizontal
SDA-4.7k1: 4.7k; R_Axial_DIN0207_L6.3mm_D2.5mm_P7.62mm_Horizontal
SW1: SW_Push; PinSocket_1x02_P2.54mm_Vertical

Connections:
/3.3V: 1W-4.7k1.1, J1.1, J3.1, J4.1, J5.3, J6.1, J9.2, J10.2, J13.1, J14.1, J15.1, J16.1, J16.2, J18.1, J19.3, J19.4, J20.1, SCL-4.7k1.1, SDA-4.7k1.1
/EN_ESP32: J2.15, J18.12
/ESP32-RX0: J1.12, J18.11
/ESP32-TX0: J1.13, J18.9
/GPIO2: J1.4, J18.3
/GPIO4: 1W-4.7k1.2, J1.5, J13.3, J14.3
/GPIO5: J1.8, J9.6
/GPIO12: J2.4, J18.4
/GPIO13: J2.3, J6.5, J16.5
/GPIO14: J2.5, J6.4, J16.4
/GPIO15: J1.3, J18.6
/GPIO16: J1.6, J4.3
/GPIO17: J1.7, J4.2
/GPIO18: J1.9, J9.5
/GPIO19: J1.10, J9.4
/GPIO21: J1.11, J5.2, J15.3, J17.1, J19.5, J20.3, SDA-4.7k1.2
/GPIO22: J1.14, J5.1, J15.4, J17.2, J18.5, J19.6, J20.4, SCL-4.7k1.2
/GPIO23: J1.15, J9.3
/GPIO25: J2.8, J18.8
/GPIO26: J2.7, J18.7
/GPIO27: J2.6, SW1.2
/GPIO32: J2.10, J3.3
/GPIO33: J2.9, J3.2
/GPIO34: J2.12, J6.6, J16.6
/GPIO35: J2.11, J18.10
GND: J1.2, J2.2, J3.4, J4.4, J5.4, J6.2, J6.3, J9.1, J10.1, J13.2, J14.2, J15.2, J16.3, J18.2, J19.1, J19.2, J20.2, SW1.1
unnamed: J11.1, J11.2
unnamed: J11.3, J11.4
unnamed: J11.5, J11.6
unnamed: J11.7, J11.8
unnamed: J7.1, J11.9
unnamed: J7.2, J11.10
unnamed: J7.3, J11.11
unnamed: J7.4, J11.12
unnamed: J12.1, J12.2
unnamed: J12.3, J12.4
unnamed: J12.5, J12.6
unnamed: J12.7, J12.8
unnamed: J8.1, J12.9
unnamed: J8.2, J12.10
unnamed: J8.3, J12.11
unnamed: J8.4, J12.12

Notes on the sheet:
Scale-Module
HX711-Scale2
DS18B20 Hive2
DS18B20 Hive1
SHT40 Ambient
ESP32-30Pin
HX711-Scale 1

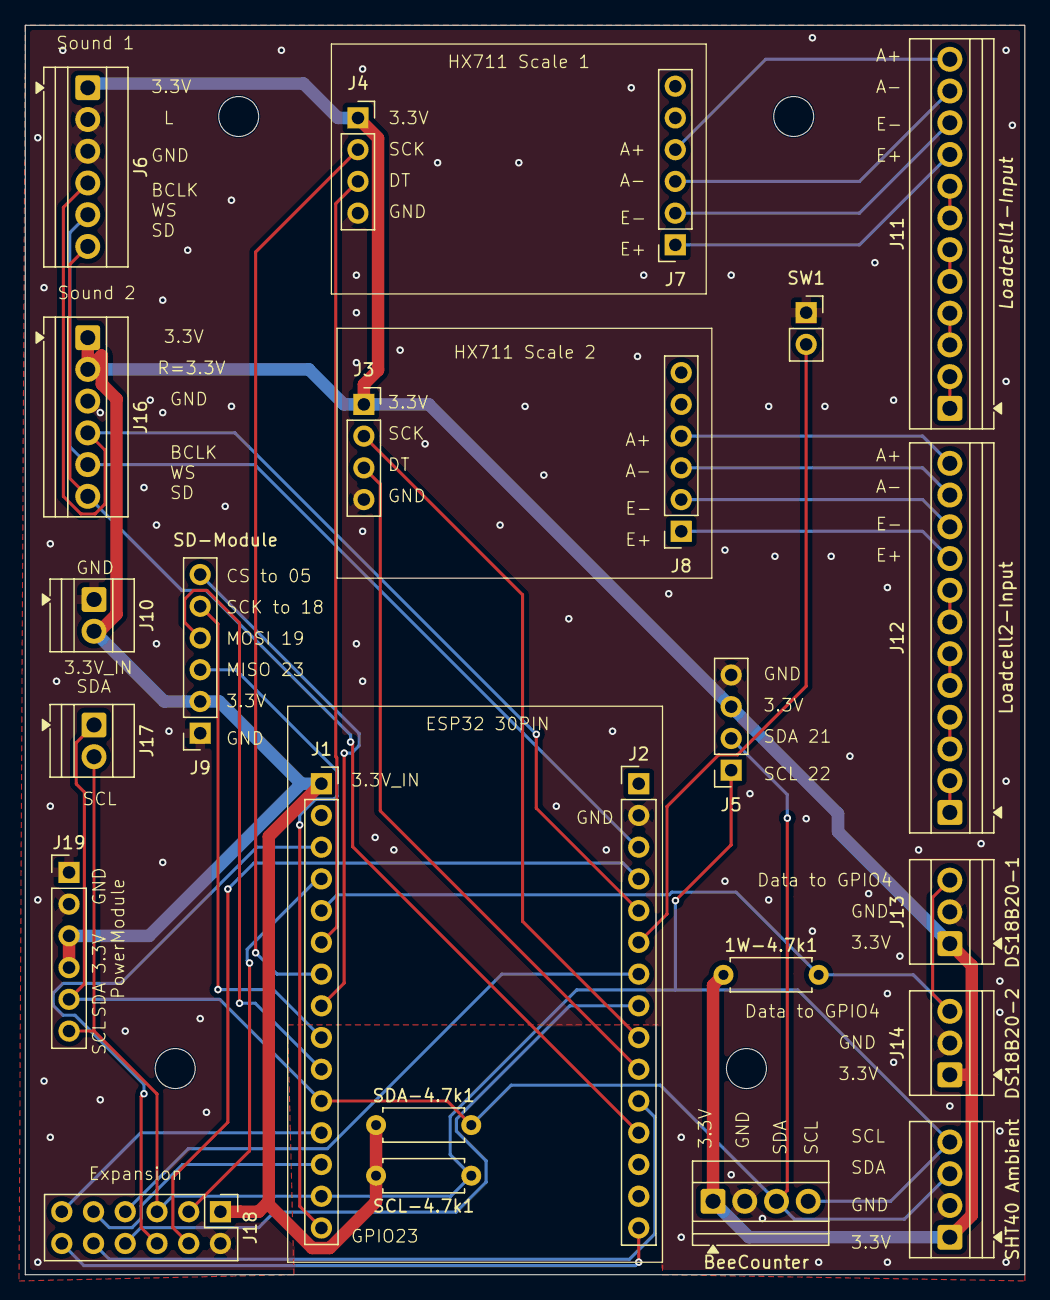
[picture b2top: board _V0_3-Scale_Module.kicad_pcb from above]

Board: 2 copper layers, 80.0 x 100.0 mm, 28 parts (1 on the bottom side), 42 nets.

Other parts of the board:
m3-bl, m3-br, m3-tl, m3-tr: MountingHole_3.2mm_M3

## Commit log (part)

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2026-04-30 Initial HiveScale project structure
2026-04-30 test-commands
2026-04-30 Updated API-URL
2026-05-01 Modified structure
2026-05-01 Added OTA firmware updates
2026-05-01 Fixed Typo
2026-05-01 Fiylxed typos, added workflow for image creation
2026-05-01 Fixed workflow
2026-05-01 Restructuring
2026-05-04 Updated firmware-backend communication, ota updates and ota calibration
2026-05-04 Ignore secrets.h
2026-05-04 gitignore
2026-05-04 Updated readme and added time-endpoint to backend.
2026-05-04 Added serial print for debugging
2026-05-04 Integrated OTA-Updates, Initial Work on Multi-User-Authentication
2026-05-05 Backend Updates for HivePal
2026-05-05 Updated build workflow
2026-05-05 Updated for User-Management
2026-05-05 Added api-key-requierement to endpoints
2026-05-05 Updated for diagram
2026-05-05 Updated readme.
2026-05-06 Optimized flash usage
2026-05-06 Added Documentation
2026-05-06 Updated documentation
2026-05-06 Added calibration mode + endpoints
2026-05-07 Added Documentation and incresed factory-reset-button-timer
2026-05-07 Added wiring instruction for bridge
2026-05-07 Added off Grid mode
2026-05-07 updated req
2026-05-08 added off-grid firmware, backend and database migration
2026-05-08 Added PWRKEY from LTE Modem
2026-05-08 Added breakout pcb design
2026-05-08 repo-restructering
2026-05-08 Commented out optional wifi settings
2026-05-08 Updated calibration Endpoints
2026-05-12 Added wiring diagram
2026-05-13 Updated gitignore
2026-05-14 PCB_V0 known issues
2026-05-14 added fotos
2026-05-14 fixed link
2026-05-14 formatting
2026-05-14 layout
2026-05-14 layout2
2026-05-14 typo...
2026-05-16 Improved SD cache
2026-05-16 Waeninf and Iteration
2026-05-16 removed old pcb files, updated notice
2026-05-24 updated to do list
2026-05-24 removed pcb files
2026-05-26 Added alarm rules via insights.py
2026-05-26 Uopdated BOM
2026-05-26 Updated bom
2026-05-26 Firmware AP-Mode update
2026-05-27 Added fft for audio processing, db migration, backend handling
2026-05-27 bugfixes
2026-05-27 bugfix
2026-05-27 Added tldr for insight sources
2026-05-27 Added V0.2 PCB-Files
2026-05-28 Added BeeCounter to insights.py
2026-05-28 fixed built error
2026-05-28 Split HiveScale firmware-behemoth into multiple parts
2026-05-28 bugfixe
2026-05-30 Optimized build-size
2026-05-30 Updated FW V number
2026-05-31 Added FW upload endpoint + migration
2026-05-31 OTA-fix
2026-05-31 Updated fw version number
2026-06-01 Added Mockup-Server for validation
2026-06-01 Bugfixing
2026-06-01 Use secrets from .env
2026-06-02 added pcb files and documentation
2026-06-02 Added V0_3 PCB design (untested)
2026-06-02 Added DDOS protection
2026-06-02 added claude.md
2026-06-02 Added fix to remove wifi password
2026-06-02 auto-adding firmware version to .bin
2026-06-02 RTC attribute fix
2026-06-02 added tls to firmware
2026-06-02 removed claim code expsure
2026-06-03 added jwt secrets and per device keys for hivescale integration
2026-06-03 updated git-ignore
2026-06-04 updated fft sending
2026-06-04 silkscreen error
2026-06-05 removed dc-offset from sound measurement
2026-06-05 added history to insights.py and database
2026-06-05 modified history tracking
2026-06-08 added endpoints to import data downoladed from sd-card
2026-06-08 Arduino-ESP32 3.x / ESP-IDF 5.x migration
2026-06-08 Changed platform to release
2026-06-08 updated doc
2026-06-08 case-insensitive header name collision on build for macos
2026-06-09 added temp-compensation as input to insights module
2026-06-09 replaced linear temp comp with ema
2026-06-09 updated ema
2026-06-09 fixed last seen issue
2026-06-10 optimized microphone code and corrected dc-removal
2026-06-10 added funding
2026-06-11 removed tare in favor of calibration wizard
2026-06-11 added acceleration sensor
2026-06-11 update fw version
2026-06-12 removed wired acc sensor, added BLE-sensor-module and pairing
2026-06-13 fix: exempt /measurements/import from MaxBodySizeMiddleware
    The 256 KB body-size guard only exempted /firmware uploads, so bulk
    SD-card imports forwarded by the HivePal backend (chunks of up to 5 000
    measurements, ~1–1.5 MB of JSON) were rejected with 413 "Request body
    too large".
    The import endpoint is already protected by require_hivepal_service_key
    + require_user_id and structurally capped by MEASUREMENT_IMPORT_MAX, so
2026-06-13 chore: ignore claude-bundles/ packaging directory
2026-06-13 fix(battery): clear MAX17048 sticky ALRT bit after each read
    The ALRT flag in the MAX17048 CONFIG register is sticky — once set it
    stays high even after SOC recovers above the alert threshold. Reading
    the flag without clearing it caused the dashboard to show "Alarm"
    permanently regardless of actual battery level.
    After reading getAlert(), call clearAlert() so the chip re-evaluates
    on its next internal ModelGauge cycle and only re-asserts the bit if
2026-06-13 updated fw version
2026-06-13 updated v0.3 pcb design
2026-06-14 Add KiCad schematic for HOLYIOT25015 nRF54L15 module
    Reconstructed from the HOLYIOT25015V1.0 PDF schematic. Includes all
    components: nRF54L15 MCU (49-pin), LIS2DH12, LPS22HB, SHT40-AD1B-R2,
    CR2032 battery switch (SI2301), 32 MHz / 32.768 kHz crystals, RF
    matching network (L3/L4/C11/C13/A1 ESD), RGB LED, push-button, SWD
    debug connectors, and all associated passives.
    https://claude.ai/code/session_012byMJWHd6Bj8gUwvTH8Mqb
2026-06-14 Fix GPIO pin assignments on HOLYIOT25015 schematic
    Cross-referenced against HOLYIOT-25008 Zephyr board support files
    (holyiot_25008_nrf54l15-pinctrl.dtsi / _common.dtsi) for confirmed pins,
    and inferred the 25015-only additions (LPS22HB CS, INT_DRDY).
    Key corrections:
    - P2.02 → SDI (MOSI), was BUTTON
    - P2.03 → INT2 (LIS2DH12 IRQ2), was CS_LPS22HB

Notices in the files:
README.md:
License:
MIT © 2026 Maximilian Nitschke
